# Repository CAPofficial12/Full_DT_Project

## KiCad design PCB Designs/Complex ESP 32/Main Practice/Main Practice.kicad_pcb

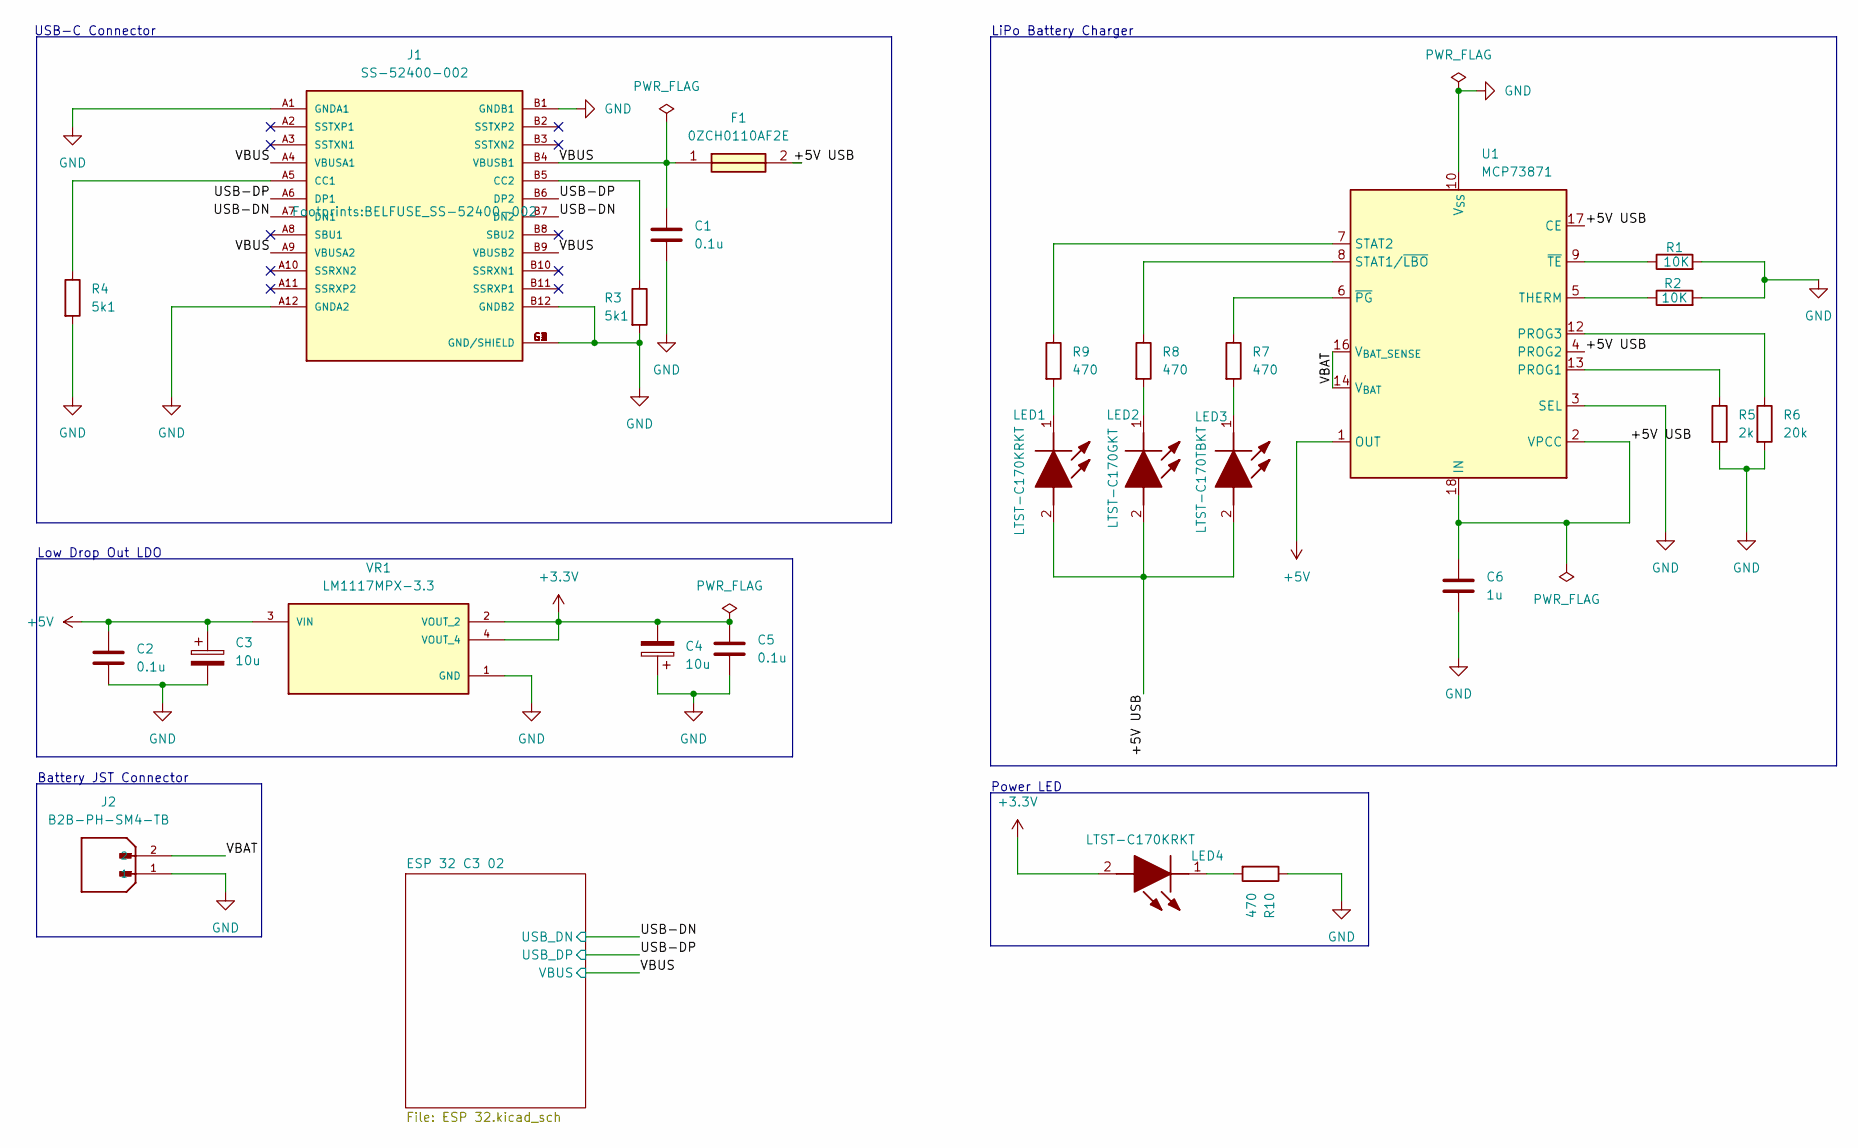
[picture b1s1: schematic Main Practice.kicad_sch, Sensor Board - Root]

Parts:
C1, C2, C5: 0.1u; C_0805_2012Metric
C3, C4: 10u; T491A
C6: 1u; C_0805_2012Metric
F1: 0ZCH0110AF2E; FUSC3226X100N; Manufacturer_Part_Number 0ZCH0110AF2E
J1: SS-52400-002; BELFUSE_SS-52400-002; PARTREV A0
J2: B2B-PH-SM4-TB; JST_B2B-PH-SM4-TB; PARTREV N/A
LED1, LED4: LTST-C170KRKT; LEDC2012X120N; Manufacturer_Part_Number LTST-C170KRKT; Mouser Part Number 859-LTST-C170KRKT
LED2: LTST-C170GKT; LEDC2012X120N; Manufacturer_Part_Number LTST-C170GKT; Mouser Part Number 859-LTST-C170GKT
LED3: LTST-C170TBKT; LEDC2012X120N; Manufacturer_Part_Number LTST-C170TBKT; Mouser Part Number 859-LTST-C170TBKT
R1, R2: 10K; R_0805_2012Metric
R3, R4: 5k1; R_0805_2012Metric
R5: 2k; R_0805_2012Metric
R6: 20k; R_0805_2012Metric
R7, R8, R9, R10: 470; R_0805_2012Metric
U1: MCP73871; QFN-20-1EP_4x4mm_P0.5mm_EP2.5x2.5mm
VR1: LM1117MPX-3.3; VREG_LM1117MPX-3.3

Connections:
+3.3V: C4.2, C5.1, LED4.2 (A), VR1.2 (VOUT_2), VR1.4 (VOUT_4); also elsewhere on the board
+5V: C2.2, C3.1, U1.1 (OUT), U1.20 (OUT), VR1.3 (VIN)
/+5V USB: C6.1, F1.2, LED1.2 (A), LED2.2 (A), LED3.2 (A), U1.2 (VPCC), U1.4 (PROG2), U1.17 (CE), U1.18 (IN), U1.19 (IN)
/USB-DN: J1.A7 (DN1), J1.B7 (DN2); also elsewhere on the board
/USB-DP: J1.A6 (DP1), J1.B6 (DP2); also elsewhere on the board
/VBAT: J2.2, U1.14 (V_{BAT}), U1.15 (V_{BAT}), U1.16 (V_{BAT_SENSE})
/VBUS: C1.1, F1.1, J1.A4 (VBUSA1), J1.A9 (VBUSA2), J1.B4 (VBUSB1), J1.B9 (VBUSB2); also elsewhere on the board
GND: C1.2, C2.1, C3.2, C4.1, C5.2, C6.2, J1.A1 (GNDA1), J1.A12 (GNDA2), J1.B1 (GNDB1), J1.B12 (GNDB2), J1.G1 (GND/SHIELD), J1.G2 (GND/SHIELD), J1.G3 (GND/SHIELD), J1.G4 (GND/SHIELD), J1.S1 (GND/SHIELD), J1.S2 (GND/SHIELD), J1.S3 (GND/SHIELD), J1.S4 (GND/SHIELD), J2.1, R1.2, R2.2, R3.2, R4.2, R5.2, R6.2, R10.1, U1.3 (SEL), U1.10 (V_{SS}), U1.11 (V_{SS}), U1.21 (V_{SS}), VR1.1 (GND); also elsewhere on the board
unnamed: J1.A5 (CC1), R4.1
unnamed: J1.B5 (CC2), R3.1
unnamed: LED1.1 (K), R9.2
unnamed: LED2.1 (K), R8.2
unnamed: LED3.1 (K), R7.2
unnamed: LED4.1 (K), R10.2
unnamed: R5.1, U1.13 (PROG1)
unnamed: R6.1, U1.12 (PROG3)
unnamed: R8.1, U1.8 (STAT1/~LBO)
unnamed: R9.1, U1.7 (STAT2)
unnamed: R2.1, U1.5 (THERM)
unnamed: R7.1, U1.6 (~PG)
unnamed: R1.1, U1.9 (~TE)

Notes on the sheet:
USB-C Connector
Power LED
Battery JST Connector
LiPo Battery Charger
Low Drop Out LDO

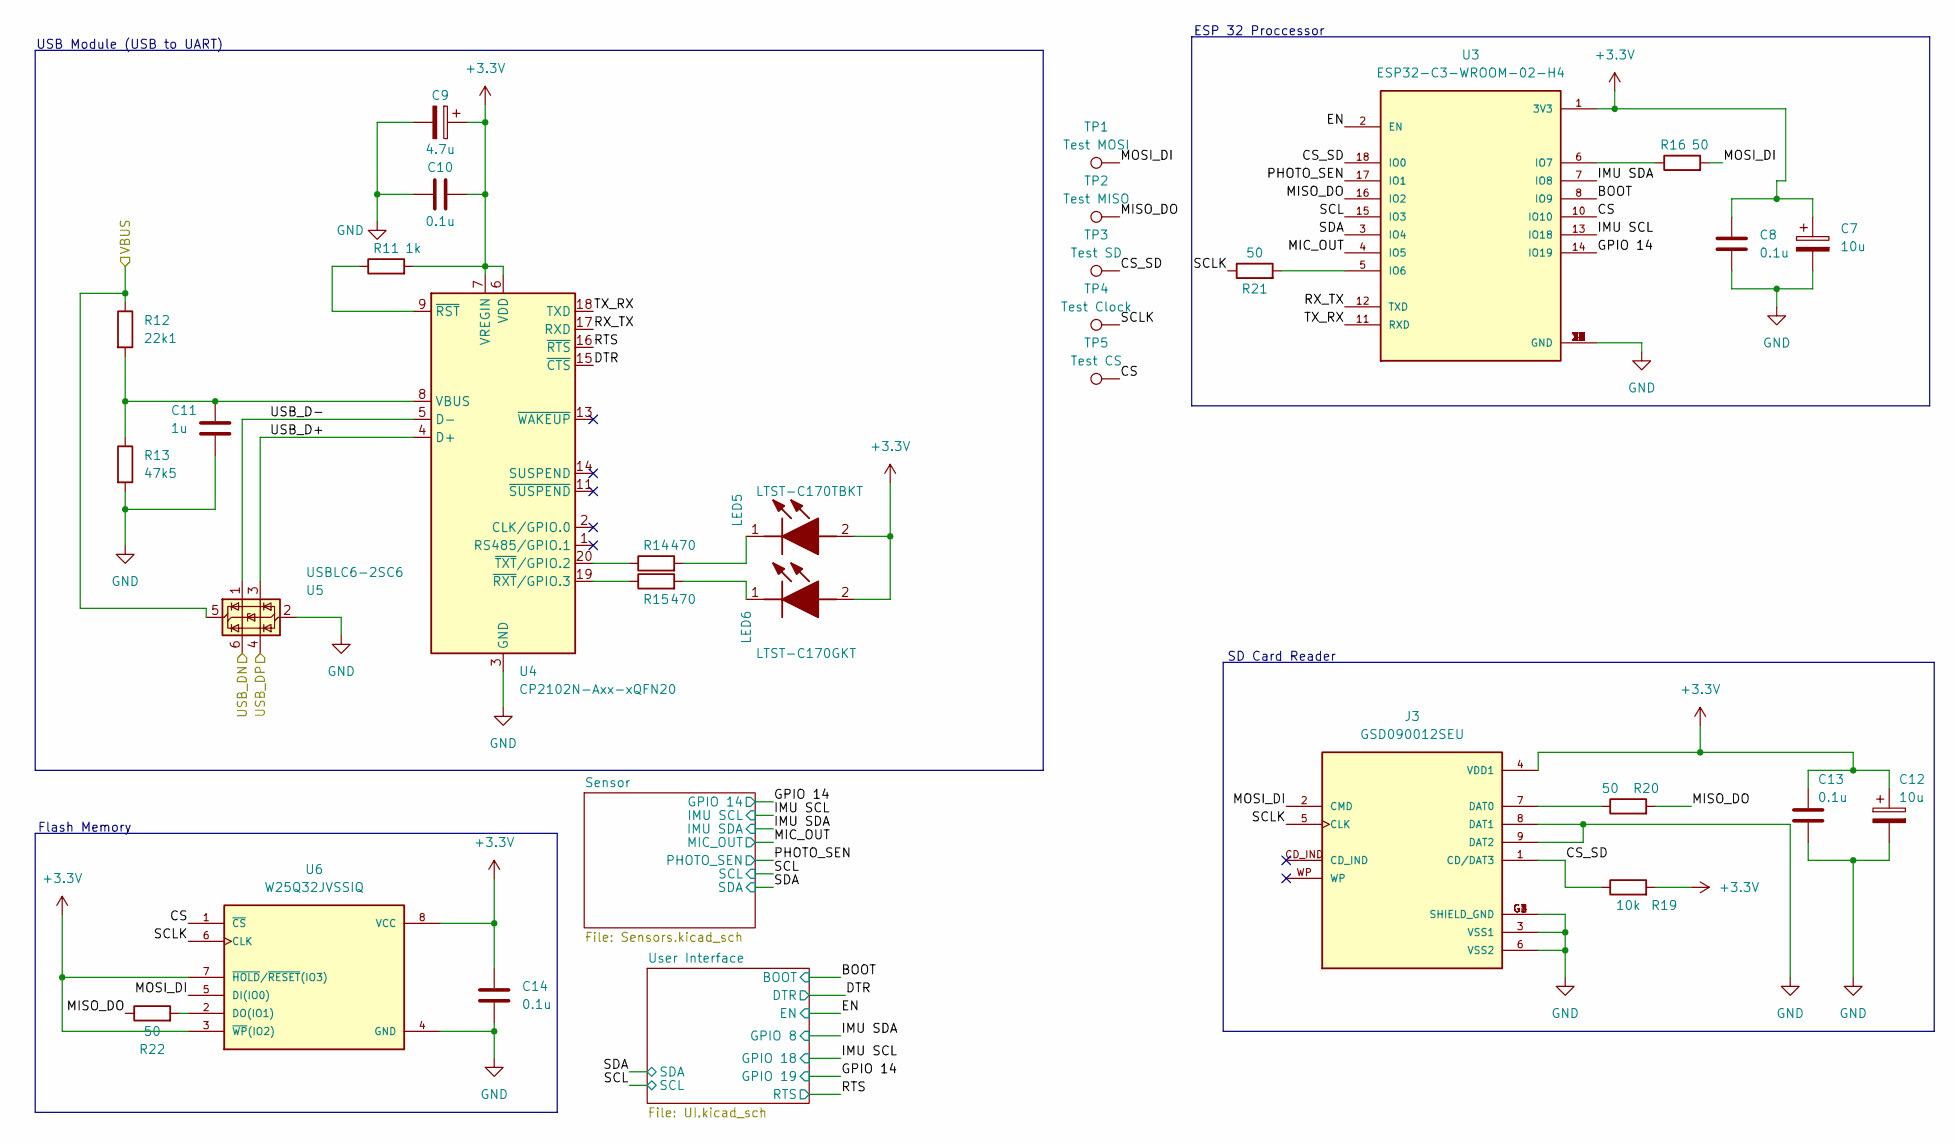
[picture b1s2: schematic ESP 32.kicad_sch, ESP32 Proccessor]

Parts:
C7, C12: 10u; T491A
C8, C10, C13, C14: 0.1u; C_0805_2012Metric
C9: 4.7u; T491A
C11: 1u; C_0805_2012Metric
J3: GSD090012SEU; AMPHENOL_GSD090012SEU; PARTREV E
LED5: LTST-C170TBKT; LEDC2012X120N; Manufacturer_Part_Number LTST-C170TBKT; Mouser Part Number 859-LTST-C170TBKT
LED6: LTST-C170GKT; LEDC2012X120N; Manufacturer_Part_Number LTST-C170GKT; Mouser Part Number 859-LTST-C170GKT
R11: 1k; R_0805_2012Metric
R12: 22k1; R_0805_2012Metric
R13: 47k5; R_0805_2012Metric
R14, R15: 470; R_0805_2012Metric
R16, R20, R21, R22: 50; R_0805_2012Metric
R19: 10k; R_0805_2012Metric
TP1: Test MOSI; TestPoint_Pad_D1.0mm
TP2: Test MISO; TestPoint_Pad_D1.0mm
TP3: Test SD; TestPoint_Pad_D1.0mm
TP4: Test Clock; TestPoint_Pad_D1.0mm
TP5: Test CS; TestPoint_Pad_D1.0mm
U3: ESP32-C3-WROOM-02-H4; MODULE_ESP32-C3-WROOM-02-H4
U4: CP2102N-Axx-xQFN20; SiliconLabs_QFN-20-1EP_3x3mm_P0.5mm_EP1.8x1.8mm
U5: USBLC6-2SC6; SOT-23-6
U6: W25Q32JVSSIQ; SOIC127P790X216-8N; M_PART_NUMBER W25QXX

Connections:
+3.3V: C7.1, C8.1, C9.1, C10.2, C12.1, C13.1, C14.1, J3.4 (VDD1), LED5.2 (A), LED6.2 (A), R11.2, R19.2, U3.1 (3V3), U4.6 (VDD), U4.7 (VREGIN), U6.3 (~WP(IO2)), U6.7 (~HOLD/~RESET(IO3)), U6.8 (VCC); also elsewhere on the board
/ESP 32 C3 02/BOOT: U3.8 (IO9); also elsewhere on the board
/ESP 32 C3 02/CS: TP5.1 (1_1), U3.10 (IO10), U6.1 (~CS)
/ESP 32 C3 02/CS_SD: J3.1 (CD/DAT3), R19.1, TP3.1 (1_1), U3.18 (IO0)
/ESP 32 C3 02/DTR: U4.15 (~CTS); also elsewhere on the board
/ESP 32 C3 02/EN: U3.2 (EN); also elsewhere on the board
/ESP 32 C3 02/GPIO 14: U3.14 (IO19); also elsewhere on the board
/ESP 32 C3 02/IMU SCL: U3.13 (IO18); also elsewhere on the board
/ESP 32 C3 02/IMU SDA: U3.7 (IO8); also elsewhere on the board
/ESP 32 C3 02/MIC_OUT: U3.4 (IO5); also elsewhere on the board
/ESP 32 C3 02/MISO_DO: R20.2, R22.1, TP2.1 (1_1), U3.16 (IO2)
/ESP 32 C3 02/MOSI_DI: J3.2 (CMD), R16.2, TP1.1 (1_1), U6.5 (DI(IO0))
/ESP 32 C3 02/PHOTO_SEN: U3.17 (IO1); also elsewhere on the board
/ESP 32 C3 02/RTS: U4.16 (~RTS); also elsewhere on the board
/ESP 32 C3 02/RX_TX: U3.12 (TXD), U4.17 (RXD)
/ESP 32 C3 02/SCL: U3.15 (IO3); also elsewhere on the board
/ESP 32 C3 02/SCLK: J3.5 (CLK), R21.1, TP4.1 (1_1), U6.6 (CLK)
/ESP 32 C3 02/SDA: U3.3 (IO4); also elsewhere on the board
/ESP 32 C3 02/TX_RX: U3.11 (RXD), U4.18 (TXD)
/ESP 32 C3 02/USB_D+: U4.4 (D+), U5.3 (I/O2)
/ESP 32 C3 02/USB_D-: U4.5 (D-), U5.1 (I/O1)
/USB-DN: U5.6 (I/O1); also elsewhere on the board
/USB-DP: U5.4 (I/O2); also elsewhere on the board
/VBUS: R12.1, U5.5 (VBUS); also elsewhere on the board
GND: C7.2, C8.2, C9.2, C10.1, C11.2, C12.2, C13.2, C14.2, J3.3 (VSS1), J3.6 (VSS2), J3.8 (DAT1), J3.9 (DAT2), J3.G1 (SHIELD_GND), J3.G2 (SHIELD_GND), J3.G3 (SHIELD_GND), J3.G4 (SHIELD_GND), R13.2, U3.9 (GND), U3.19 (GND), U3.20 (GND), U3.21 (GND), U3.22 (GND), U3.23 (GND), U3.24 (GND), U3.25 (GND), U3.26 (GND), U3.27 (GND), U3.28 (GND), U3.29 (GND), U3.30 (GND), U3.31 (GND), U3.32 (GND), U3.33 (GND), U3.34 (GND), U3.35 (GND), U3.36 (GND), U3.37 (GND), U3.38 (GND), U3.39 (GND), U4.3 (GND), U4.12 (GND), U4.21 (GND), U5.2 (GND), U6.4 (GND); also elsewhere on the board
unnamed: J3.7 (DAT0), R20.1
unnamed: LED5.1 (K), R14.2
unnamed: LED6.1 (K), R15.2
unnamed: R21.2, U3.5 (IO6)
unnamed: R16.1, U3.6 (IO7)
unnamed: C11.1, R12.2, R13.1, U4.8 (VBUS)
unnamed: R11.1, U4.9 (~RST)
unnamed: R15.1, U4.19 (~RXT/GPIO.3)
unnamed: R14.1, U4.20 (~TXT/GPIO.2)
unnamed: R22.2, U6.2 (DO(IO1))

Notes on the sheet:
ESP 32 Proccessor
Flash Memory
SD Card Reader
USB Module (USB to UART)

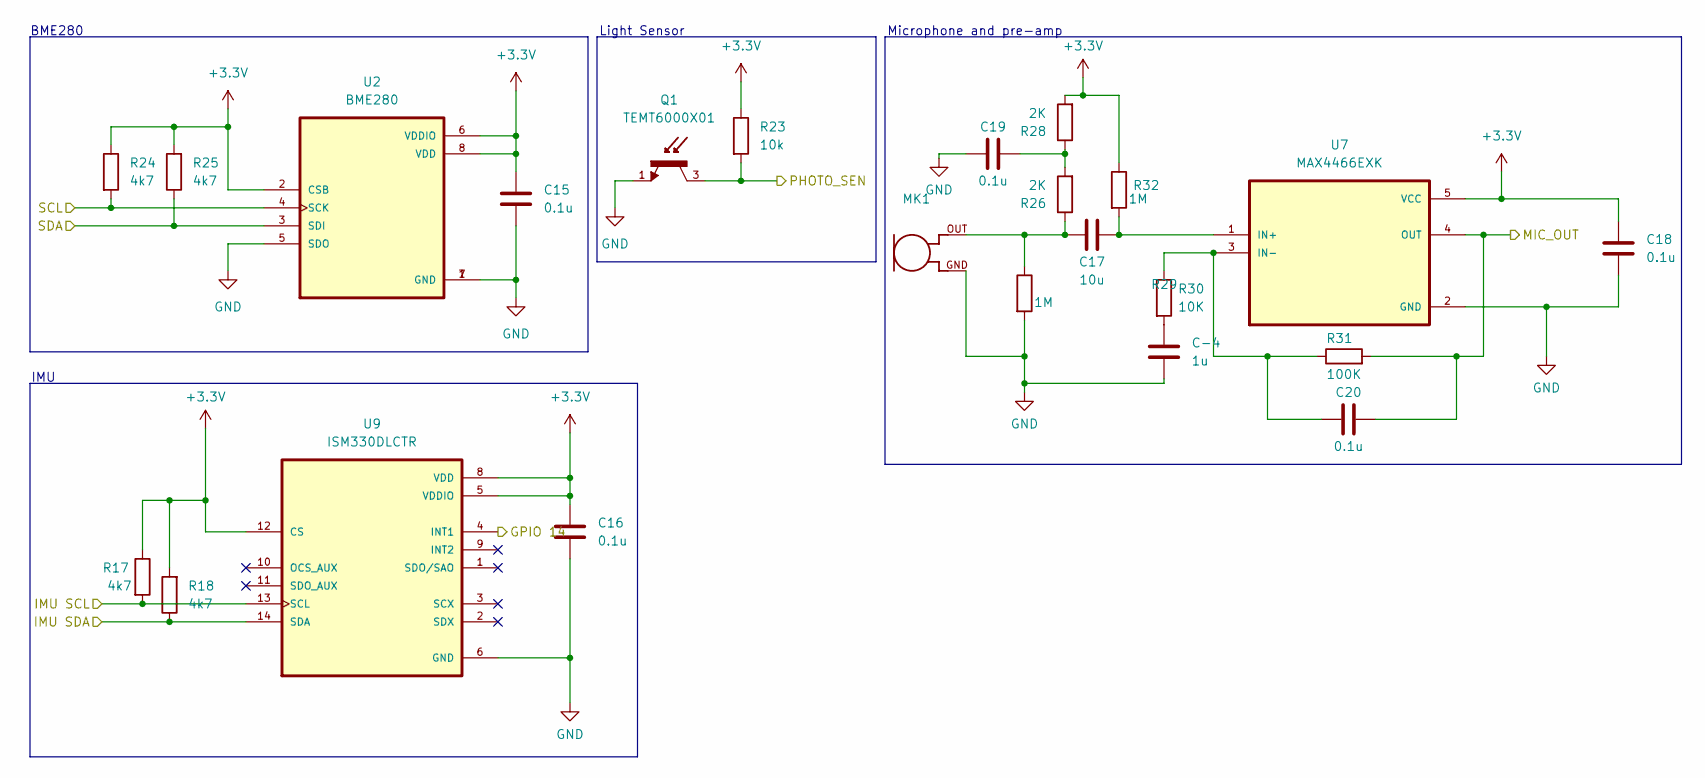
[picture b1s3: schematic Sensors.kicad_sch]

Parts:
C15, C16, C18, C19, C20: 0.1u; C_0805_2012Metric
C17: 10u; C_0805_2012Metric
C-4: 1u; C_0805_2012Metric
MK1: CMC-5042PF-AC; CUI_CMC-5042PF-AC
Q1: TEMT6000X01; TRANS_TEMT6000X01; PARTREV 1.9
R17, R18, R24, R25: 4k7; R_0805_2012Metric
R23: 10k; R_0805_2012Metric
R26, R28: 2K; R_0805_2012Metric
R29, R32: 1M; R_0805_2012Metric
R30: 10K; R_0805_2012Metric
R31: 100K; R_0805_2012Metric
U2: BME280; PSON65P250X250X100-8N
U7: MAX4466EXK; SOT65P210X110-5N
U9: ISM330DLCTR; QFN50P400X400X100-21N; PARTREV 2

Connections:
+3.3V: C15.1, C16.1, C18.1, R17.1, R18.2, R23.1, R24.1, R25.2, R28.2, R32.1, U2.2 (CSB), U2.6 (VDDIO), U2.8 (VDD), U7.5 (VCC), U9.5 (VDDIO), U9.8 (VDD), U9.12 (CS); also elsewhere on the board
/ESP 32 C3 02/GPIO 14: U9.4 (INT1); also elsewhere on the board
/ESP 32 C3 02/IMU SCL: R17.2, U9.13 (SCL); also elsewhere on the board
/ESP 32 C3 02/IMU SDA: R18.1, U9.14 (SDA); also elsewhere on the board
/ESP 32 C3 02/MIC_OUT: C20.2, R31.2, U7.4 (OUT); also elsewhere on the board
/ESP 32 C3 02/PHOTO_SEN: Q1.3, R23.2; also elsewhere on the board
/ESP 32 C3 02/SCL: R24.2, U2.4 (SCK); also elsewhere on the board
/ESP 32 C3 02/SDA: R25.1, U2.3 (SDI); also elsewhere on the board
GND: C15.2, C16.2, C18.2, C19.1, C-4.2, MK1.GND, Q1.1, R29.2, U2.1 (GND), U2.5 (SDO), U2.7 (GND), U7.2 (GND), U9.6 (GND), U9.7 (GND); also elsewhere on the board
unnamed: C17.1, MK1.OUT, R26.1, R29.1
unnamed: C19.2, R26.2, R28.1
unnamed: C-4.1, R30.2
unnamed: C17.2, R32.2, U7.1 (IN+)
unnamed: C20.1, R30.1, R31.1, U7.3 (IN-)

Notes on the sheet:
Microphone and pre-amp
BME280
IMU
Light Sensor

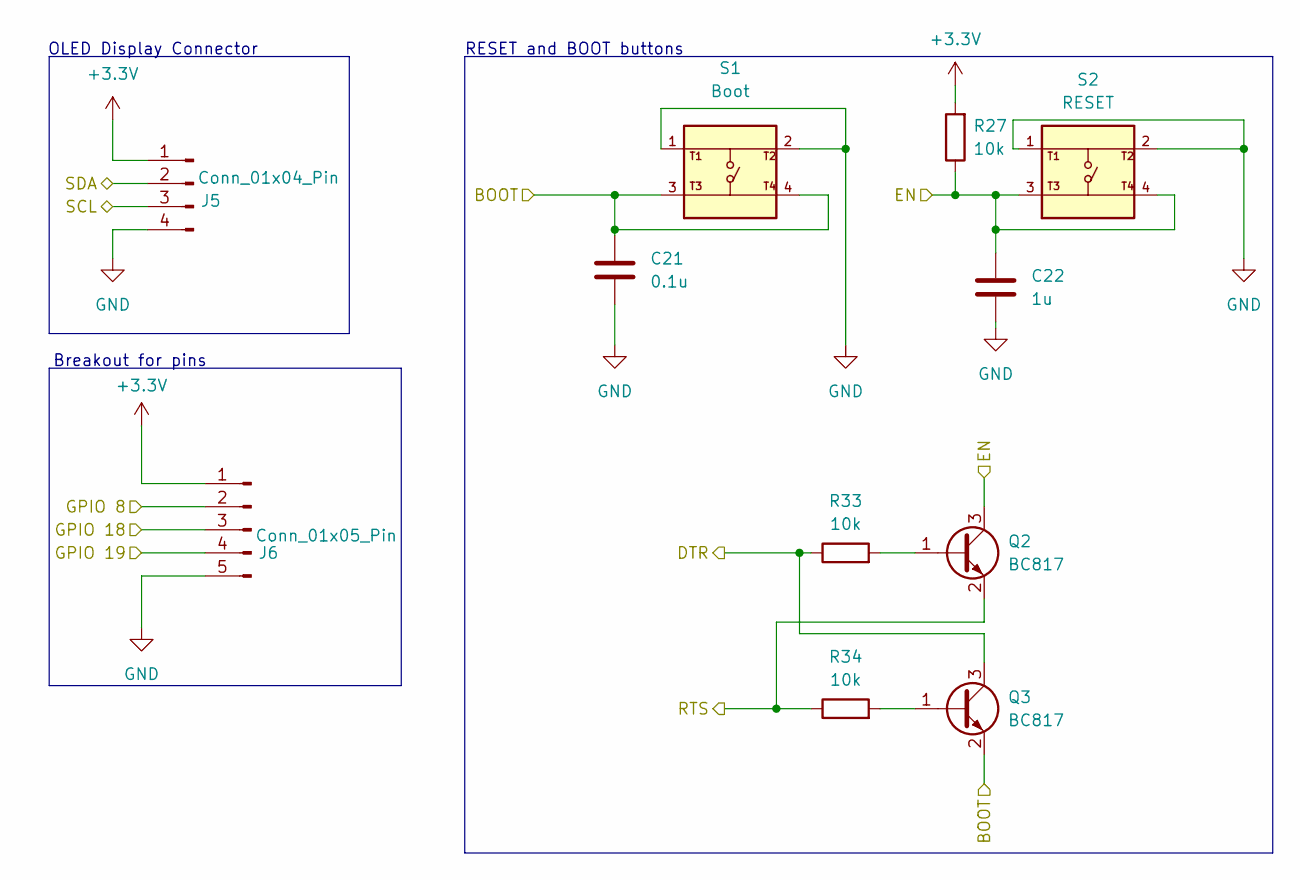
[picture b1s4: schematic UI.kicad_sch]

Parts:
C21: 0.1u; C_0805_2012Metric
C22: 1u; C_0805_2012Metric
J5: Conn_01x04_Pin; PinHeader_1x04_P2.54mm_Vertical
J6: Conn_01x05_Pin; PinHeader_1x05_P2.54mm_Vertical
Q2, Q3: BC817; SOT-23
R27, R33, R34: 10k; R_0805_2012Metric
S1: Boot; SW_USLPT2819DT2TR; PARTREV P
S2: RESET; SW_USLPT2819DT2TR; PARTREV P

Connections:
+3.3V: J5.1, J6.1, R27.2; also elsewhere on the board
/ESP 32 C3 02/BOOT: C21.1, Q3.2 (E), S1.3, S1.4; also elsewhere on the board
/ESP 32 C3 02/DTR: Q3.3 (C), R33.1; also elsewhere on the board
/ESP 32 C3 02/EN: C22.1, Q2.3 (C), R27.1, S2.3, S2.4; also elsewhere on the board
/ESP 32 C3 02/GPIO 14: J6.4; also elsewhere on the board
/ESP 32 C3 02/IMU SCL: J6.3; also elsewhere on the board
/ESP 32 C3 02/IMU SDA: J6.2; also elsewhere on the board
/ESP 32 C3 02/RTS: Q2.2 (E), R34.1; also elsewhere on the board
/ESP 32 C3 02/SCL: J5.3; also elsewhere on the board
/ESP 32 C3 02/SDA: J5.2; also elsewhere on the board
GND: C21.2, C22.2, J5.4, J6.5, S1.1, S1.2, S2.1, S2.2; also elsewhere on the board
unnamed: Q2.1 (B), R33.2
unnamed: Q3.1 (B), R34.2

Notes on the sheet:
Breakout for pins
RESET and BOOT buttons
OLED Display Connector

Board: 4 copper layers, 89 parts (0 on the bottom side), 58 nets, no tracks yet.

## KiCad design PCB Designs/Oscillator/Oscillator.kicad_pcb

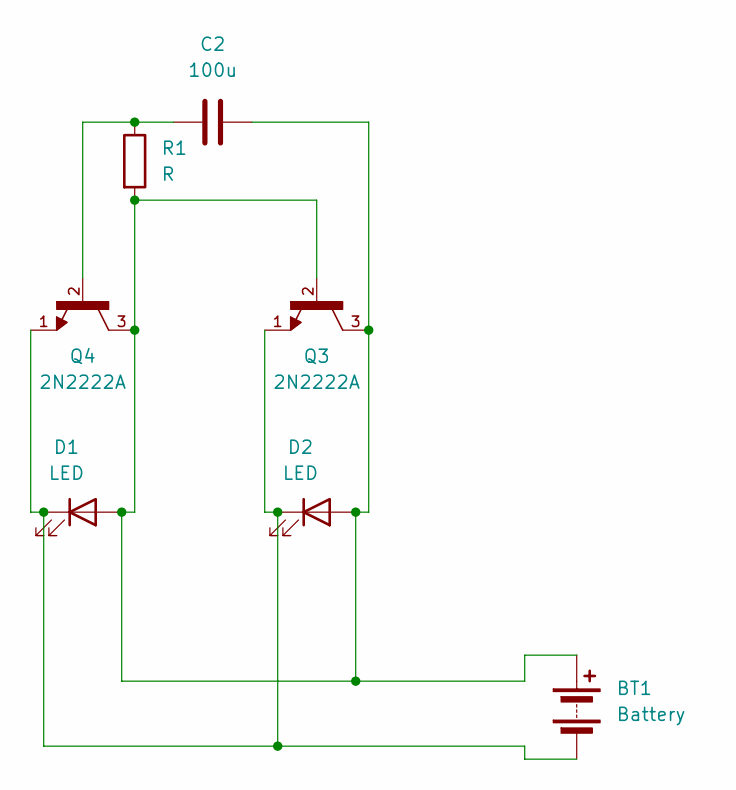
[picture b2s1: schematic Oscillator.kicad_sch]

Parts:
BT1: Battery; BatteryHolder_Bulgin_BX0034_1xAAA
C2: 100u; CP_Elec_10x10
D1, D2: LED; LED_D3.0mm
Q3, Q4: 2N2222A; TO92254P470H750-3; PARTREV N/A
R1: R; R_Axial_DIN0204_L3.6mm_D1.6mm_P2.54mm_Vertical

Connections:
unnamed: BT1.1 (+), C2.2, D1.2 (A), D2.2 (A), Q3.2, Q3.3, Q4.3, R1.2
unnamed: BT1.2 (-), D1.1 (K), D2.1 (K), Q3.1, Q4.1
unnamed: C2.1, Q4.2, R1.1

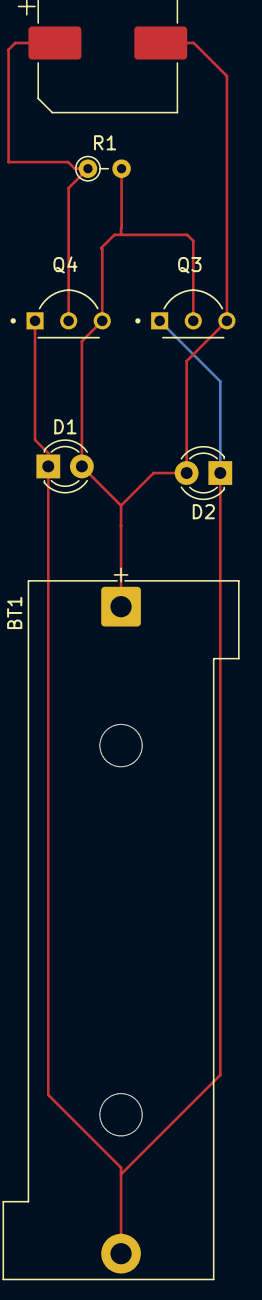
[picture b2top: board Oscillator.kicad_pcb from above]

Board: 2 copper layers, 7 parts (0 on the bottom side), 3 nets.

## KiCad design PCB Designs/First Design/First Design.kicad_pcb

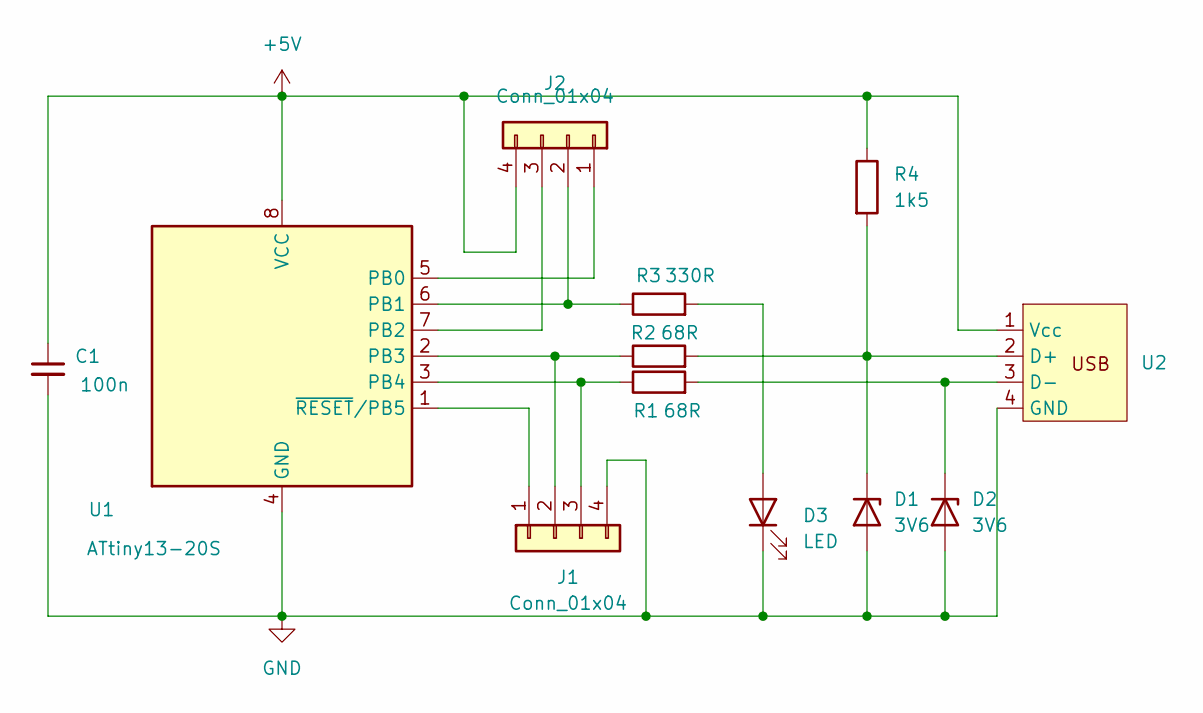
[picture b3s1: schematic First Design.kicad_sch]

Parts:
C1: 100n; C_1206_3216Metric_Pad1.33x1.80mm_HandSolder
D1, D2: 3V6; D_SOD-123F
D3: LED; LED_D3.0mm
J1, J2: Conn_01x04; SolderWire-0.127sqmm_1x04_P3.7mm_D0.48mm_OD1mm
R1, R2: 68R; R_0805_2012Metric
R3: 330R; R_0805_2012Metric
R4: 1k5; R_0805_2012Metric
U1: ATtiny13-20S; SOIC-8_5.3x5.3mm_P1.27mm
U2: pcb_usb

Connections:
+5V: C1.1, J2.4, R4.1, U1.8 (VCC), U2.1 (Vcc)
GND: C1.2, D1.2 (A), D2.2 (A), D3.1 (K), J1.4, U1.4 (GND), U2.4 (GND)
unnamed: D1.1 (K), R2.2, R4.2, U2.2 (D+)
unnamed: D2.1 (K), R1.2, U2.3 (D-)
unnamed: D3.2 (A), R3.2
unnamed: J1.1, U1.1 (~RESET/PB5)
unnamed: J1.2, R2.1, U1.2 (PB3)
unnamed: J1.3, R1.1, U1.3 (PB4)
unnamed: J2.1, U1.5 (PB0)
unnamed: J2.2, R3.1, U1.6 (PB1)
unnamed: J2.3, U1.7 (PB2)

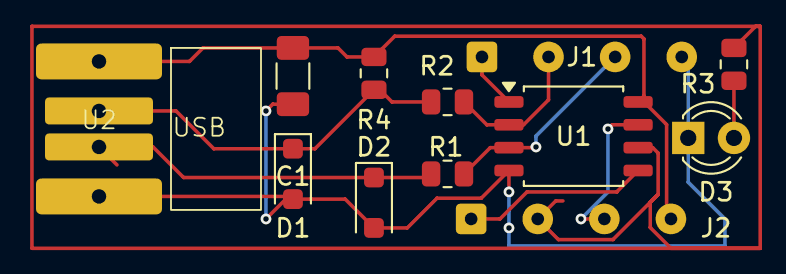
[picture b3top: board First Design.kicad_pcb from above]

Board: 2 copper layers, 12 parts (0 on the bottom side), 11 nets.

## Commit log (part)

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2026-05-04 Added Models
2026-05-04 Added My PCB Designs
2026-05-04 Removed History from PCBs
2026-05-04 Alot of uploads
2026-05-06 Finished Oscillator PCB
2026-05-06 Changed Something (i have no idea what)
2026-05-08 Developed upon esp 32 schem
2026-05-08 Saved UI
2026-05-09 Downloaded Git Plugin
2026-05-09 Figured out IK for robot leg using polar coordinates
2026-05-09 Used Random Number generator to test. passed all tests
2026-05-09 Started Schematics of footprint
2026-05-10 Made program imput based
2026-05-14 Moved all current 3d printed part designs into a folder and send to voltaat
2026-05-14 reordered components around for optimal wiring
2026-05-14 Saved all changes again
2026-05-16 Added more comments to Main code for PIDF tuning
2026-05-20 Used to calculate number of screw and of what length needed for parts
2026-05-20 Added Claude reference code to develop robot
2026-05-22 Got LED blinking using raw AVR code
2026-05-22 No idea what js happened
2026-05-22 Finished Switching LED
2026-05-22 Figured how to use the Onboard timer of the ATMega 328P
2026-05-22 Finished PWM for an LED
2026-05-23 Moved PIDF to Arduin Uno Code
2026-05-25 Added an extra bracket to the lower legs to test whether the motors run the robot or not
2026-05-25 Moved all AVR C files into a seperate folder
2026-05-25 Added servo lock test
2026-05-26 Finished Differential drive Test
2026-05-30 Added refeerence text file
2026-05-30 Setuip enviroment for Static hight PIDF
2026-05-30 Moved Files to a new folder
2026-05-30 Made IMU reading code
2026-05-30 Completed IMU reading code
2026-06-04 Added new NEA folder
2026-06-05 Servos did not work so I switched to LED. LED Test 1:
2026-06-05 LED Test 2:
2026-06-05 LED Test 3: Flickered at a lower brightness
2026-06-05 LED Test 4: The light stayed at a lower luminosity
2026-06-05 LED Test 5: Sweeping brightness Test
2026-06-05 LED Test 6: Increased delay in loop
2026-06-05 Test 7: Removed attahcment
2026-06-05 Servo Test 8: Servo and bracket boundary calibration
2026-06-05 Servo Test 9: Platform 90
2026-06-06 Servo Test 10: Moved servo.write to function and called
2026-06-06 Servo Test 11: Combined Both functions to moved to a stable position with base flat
2026-06-08 Changed Servo Pins
2026-06-10 Changed Pin allocation to accomodate test pin connection for torque + power change
2026-06-10 Motor Test 12: Optimised code for single wheel
2026-06-10 Added Year 10 Final NEA to project
2026-06-10 Moved All NEA files to seperate folders
2026-06-12 Test 12: 2nd Servo Sweep for ESP32
2026-06-12 Servo Test 13: Servo Lock on ESP32
2026-06-12 Added Static PIDF code only including servo Lock
2026-06-12 Made code to read IMU
2026-06-15 Added Motor Setup to ESP2 Code
2026-06-16 EduBot Test 14: Tested Timer, worked
2026-06-19 Completed Test Code for static PIDF
2026-06-19 Thsi is the code that is supposed to be present int the previous commit
2026-06-19 Completed Breakout board designs and wiring for esp32 motors
2026-06-19 Added MPU 6050 to wiring
2026-06-19 Made Inverse Kinematics test
    Decided to use Polar instead of ceartesian
2026-06-19 Why
    Does
    This
    Keep
    Happening
2026-06-19 Wrote basic TT motor code
